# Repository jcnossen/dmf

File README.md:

# dmf
Prototype for electrowetting and digital microfluidics

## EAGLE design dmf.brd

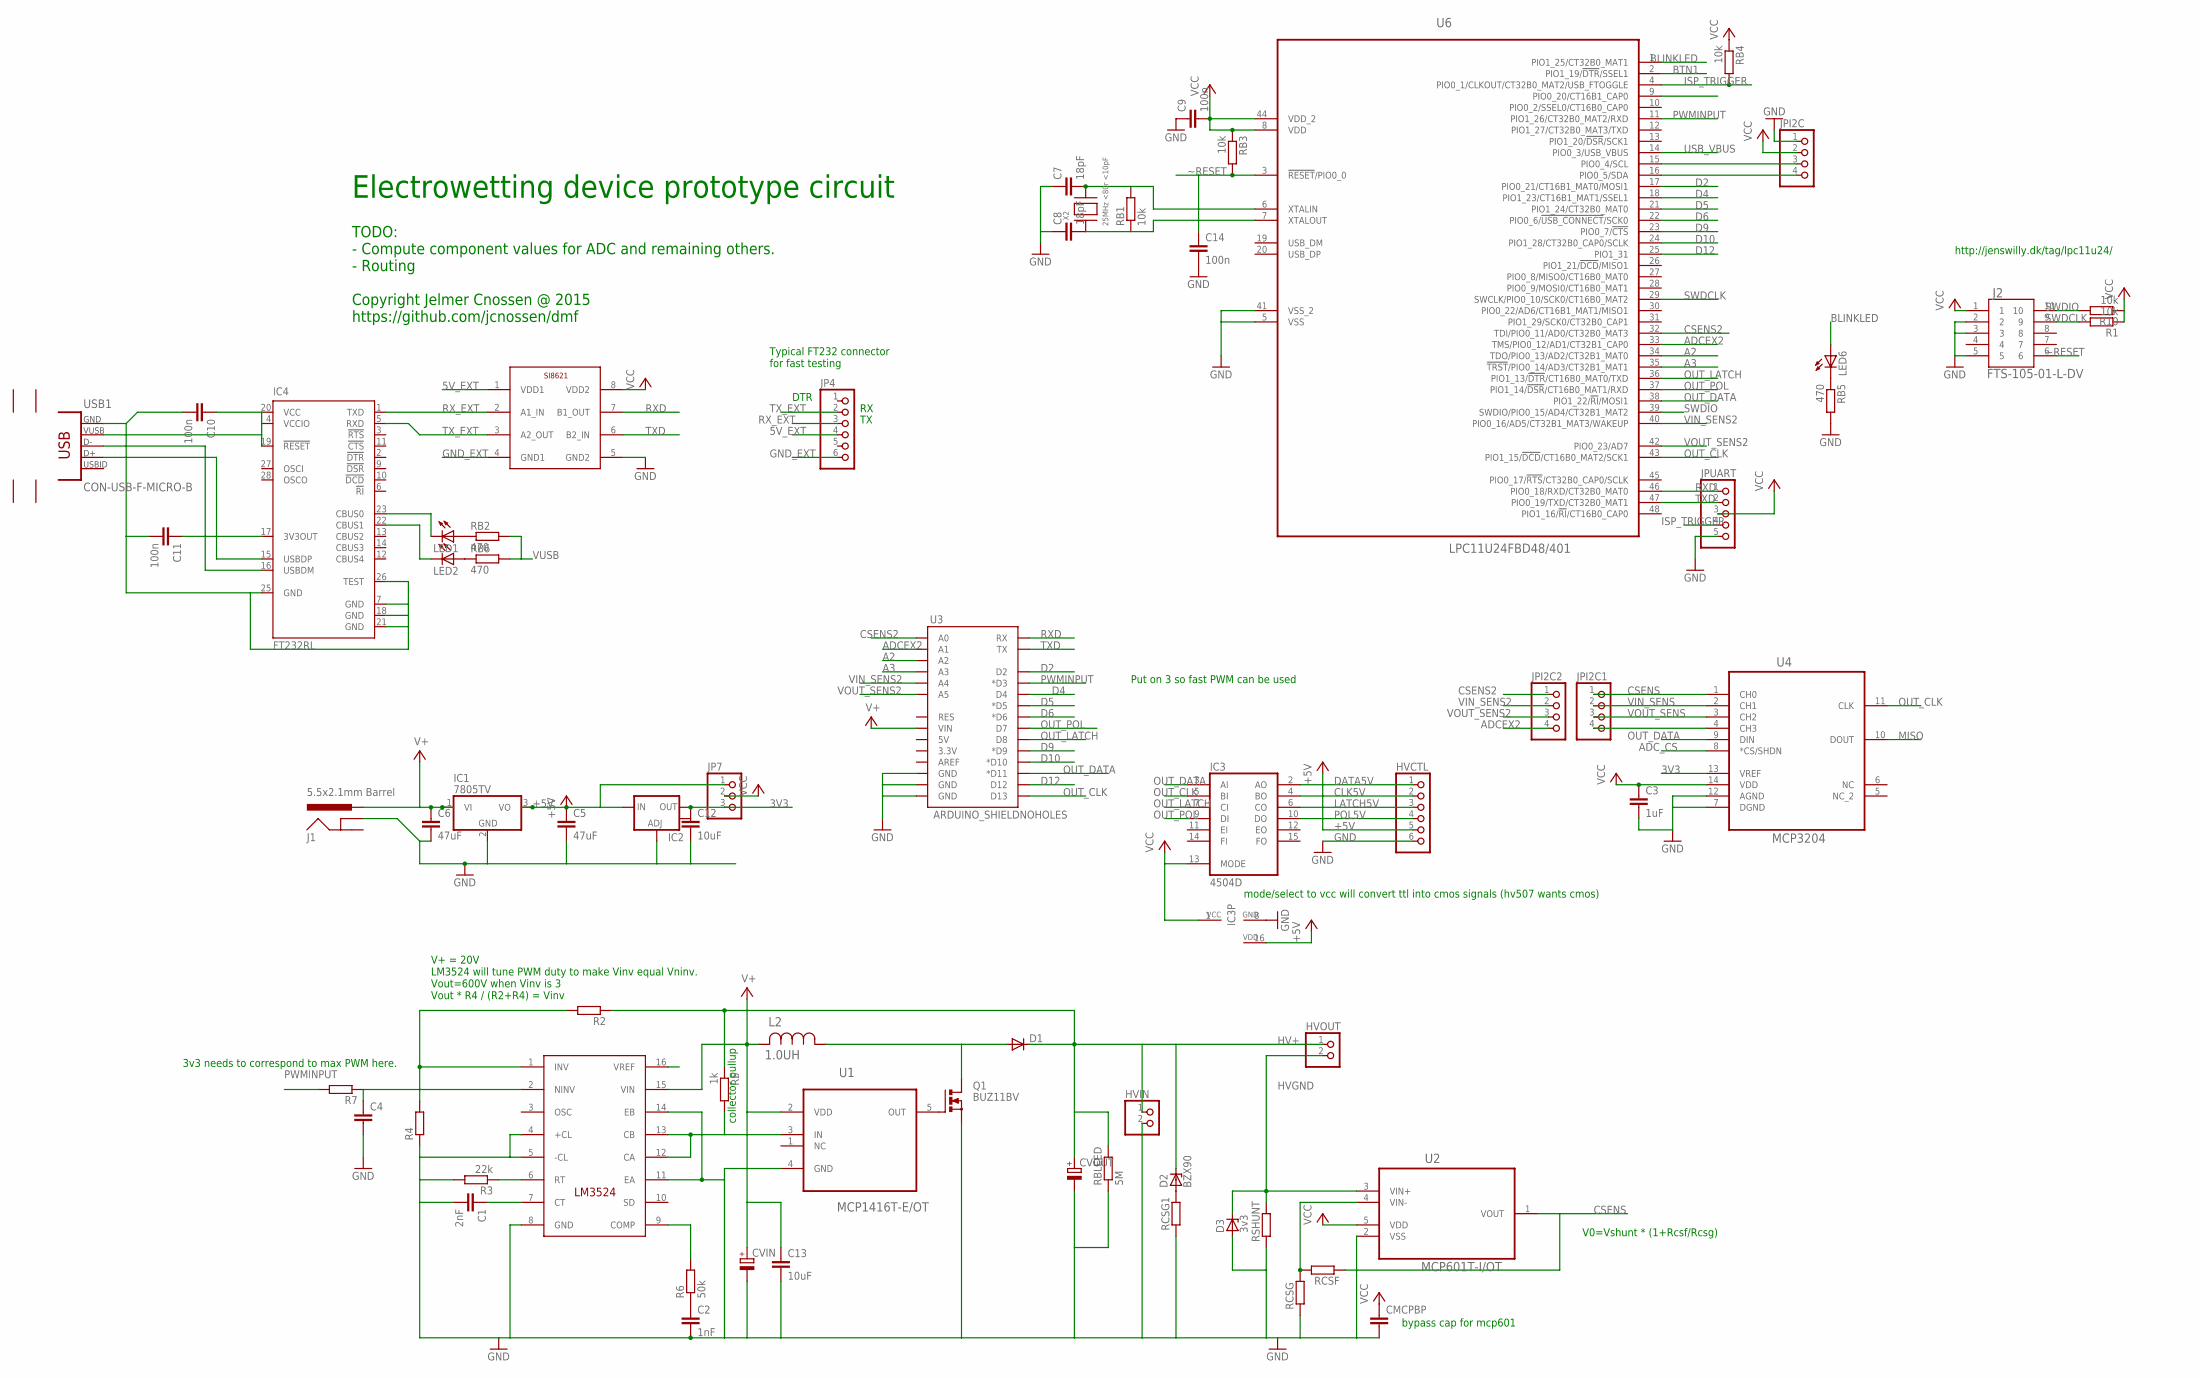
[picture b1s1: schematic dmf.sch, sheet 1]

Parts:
C1: 2nF; C0805
C2: 1nF; C0805
C3: 1uF; C0805
C4: C-EUC0805; C0805
C5, C6: 47uF; C1206
C7, C8: 18pF; C0805
C9, C10, C11, C14: 100n; C0805
C12: 10uF; C1206
C13: 10uF; C0805
CMCPBP: C-EUC0805; C0805
CVIN: CPOL-EUE7.5-18; E7,5-18
CVOUT: CPOL-EUE7.5-18; E7,5-18
D1: DIODE-SMB; SMB
D2: BZX90; DO34Z7
D3: 3v3; SMB
HVCTL: PINHD-1X06_2.54-S; 1X06-S
HVIN: PINHD-1X02_2.54; 1X02
HVOUT: PINHD-1X02_2.54; 1X02
IC1: 7805TV; TO220V
IC2: V_REG_LM1117SOT223; SOT223
IC3: 4504D; SO16
IC4: FT232RL; SSOP28
J1: 5.5x2.1mm Barrel; POWER_JACK_SMD
J2: FTS-105-01-L-DV; SAMTEC_FTS-105-01-L-DV
JP4: PINHD-1X06_2.54-S; 1X06-S
JP7: PINHD-1X03_2.54-S; 1X03-S
JPI2C, JPI2C1, JPI2C2: PINHD-1X04_2.54-S; 1X04-S
JPUART: PINHD-1X05_2.54-S; 1X05-S
L2: 1.0UH; IND_ELL6XH
LED1, LED2, LED6: LEDCHIP-LED0805; CHIP-LED0805
Q1: BUZ11BV; TO220BV
R1, R10: 10k; R0603
R2, R4, R7: R-EU_R0603; R0603
R3: 22k; R0603
R5: 1k; R0603
R6: 50k; R0603
RB1, RB3, RB4: 10k; R0603
RB2, RB6: 470; R0603
RB5: 470; R0402
RBLEED: 5M; R1206
RCSF: R-EU_R0603; R0603
RCSG: R-EU_R0603; R0603
RCSG1: R-EU_R1206; R1206
RSHUNT: R-EU_R1206; R1206
U1: MCP1416T-E/OT; SOT95P270X145-5N
U2: MCP601T-I/OT; SOT95P320X145-5N
U3: ARDUINO_SHIELDNOHOLES; DUEMILANOVE_SHIELD_NOHOLES
U4: MCP3204; SOIC127P600X175-14N
U6: LPC11U24FBD48/401; QFP50P900X900X160-48N
U$1: LM3524; SO16
U$2: SI8621AB; SO8
USB1: CON-USB-F-MICRO-B; CONN_USB_MICRO-B
X2: 25MHz <80r <10pF; NX5032

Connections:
3V3: C12.1, IC2.2 (OUT), JP7.3, U4.13 (VREF)
5V_EXT: JP4.4, U$2.1 (VDD1)
+5V: C5.1, HVCTL.5, IC1.3 (VO), IC2.3 (IN), IC3.16 (VDD), JP7.1
A2: U3.A2, U6.34 (TDO/PIO0_13/AD2/CT32B1_MAT0)
A3: U3.A3, U6.35 (!TRST!/PIO0_14/AD3/CT32B1_MAT1)
ADCEX: JPI2C1.4, U4.4 (CH3)
ADCEX2: JPI2C2.4, U3.A1, U6.33 (TMS/PIO0_12/AD1/CT32B1_CAP0)
ADC_CS: U4.8 (*CS/SHDN)
BLINKLED: LED6.A, U6.1 (PIO1_25/CT32B0_MAT1)
BTN1: U6.2 (PIO1_19/!DTR!/SSEL1)
CLK5V: HVCTL.2, IC3.4 (BO)
COLLECTOR: R5.2, U1.3 (IN), U$1.12 (CA), U$1.13 (CB)
CSENS: JPI2C1.1, RCSF.1, U2.1 (VOUT), U4.1 (CH0)
CSENS2: JPI2C2.1, U3.A0, U6.32 (TDI/PIO0_11/AD0/CT32B0_MAT3)
D2: U3.D2, U6.17 (PIO0_21/CT16B1_MAT0/MOSI1)
D4: U3.D4, U6.18 (PIO1_23/CT16B1_MAT1/SSEL1)
D5: U3.D5 (*D5), U6.21 (PIO1_24/CT32B0_MAT0)
D6: U3.D6 (*D6), U6.22 (PIO0_6/!USB_CONNECT!/SCK0)
D9: U3.D9 (*D9), U6.23 (PIO0_7/!CTS)
D10: U3.D10 (*D10), U6.24 (PIO1_28/CT32B0_CAP0/SCLK)
D12: U3.D12, U6.25 (PIO1_31)
DATA5V: HVCTL.1, IC3.2 (AO)
GND: C1.2, C2.2, C3.2, C4.2, C5.2, C6.2, C7.1, C8.1, C9.1, C12.2, C13.2, C14.2, CMCPBP.2, CVIN.-, CVOUT.-, D3.A, HVCTL.6, HVIN.2, IC1.2 (GND), IC2.1 (ADJ), IC3.8 (GND), J1.GND (GNDBREAK), J2.2, J2.3, J2.5, JPI2C.1, JPUART.5, Q1.S, R3.2, R4.1, RB5.2, RBLEED.1, RCSG.1, RCSG1.1, RSHUNT.1, U1.4 (GND), U2.2 (VSS), U3.GND@0 (GND), U3.GND@1 (GND), U3.GND@2 (GND), U4.7 (DGND), U4.12 (AGND), U6.5 (VSS), U6.41 (VSS_2), U$1.4 (+CL), U$1.5 (-CL), U$1.8 (GND), U$1.11 (EA), U$1.14 (EB), U$2.5 (GND2)
GND_EXT: C10.2, C11.2, IC4.7 (GND), IC4.18 (GND), IC4.21 (GND), IC4.25 (GND), IC4.26 (TEST), JP4.6, U$2.4 (GND1), USB1.P5 (GND)
HV+: CVOUT.+, D1.C, D2.C, HVIN.1, HVOUT.1, R2.1, R5.1, RBLEED.2
HVGND: D3.C, HVOUT.2, RSHUNT.2, U2.3 (VIN+)
ISP_TRIGGER: JPUART.4, RB4.2, U6.4 (PIO0_1/CLKOUT/CT32B0_MAT2/USB_FTOGGLE)
LATCH5V: HVCTL.3, IC3.6 (CO)
MISO: U4.10 (DOUT)
unnamed: C2.1, R6.1
unnamed: C1.1, U$1.7 (CT)
unnamed: R2.2, R4.2, U$1.1 (INV)
unnamed: R3.1, U$1.6 (RT)
unnamed: R6.2, U$1.9 (COMP)
unnamed: D1.A, L2.1, Q1.D
unnamed: Q1.G, U1.5 (OUT)
unnamed: RCSF.2, RCSG.2, U2.4 (VIN-)
unnamed: D2.A, RCSG1.2
unnamed: C4.1, R7.1, U$1.2 (NINV)
unnamed: IC4.16 (USBDM), USB1.P2 (D-)
unnamed: IC4.15 (USBDP), USB1.P3 (D+)
unnamed: C11.1, IC4.17 (3V3OUT)
unnamed: IC4.23 (CBUS0), LED1.C
unnamed: IC4.22 (CBUS1), LED2.C
unnamed: LED1.A, RB2.1
unnamed: LED2.A, RB6.1
unnamed: C8.2, RB1.1, U6.7 (XTALOUT), X2.P$1
unnamed: LED6.C, RB5.1
unnamed: C7.2, RB1.2, U6.6 (XTALIN), X2.P$2
OUT_CLK: IC3.5 (BI), U3.D13, U4.11 (CLK), U6.43 (PIO1_15/!DCD!/CT16B0_MAT2/SCK1)
OUT_DATA: IC3.3 (AI), U3.D11 (*D11), U4.9 (DIN), U6.38 (PIO1_22/!RI!/MOSI1)
OUT_LATCH: IC3.7 (CI), U3.D8, U6.36 (PIO1_13/!DTR!/CT16B0_MAT0/TXD)
OUT_POL: IC3.9 (DI), U3.D7, U6.37 (PIO1_14/!DSR!/CT16B0_MAT1/RXD)
POL5V: HVCTL.4, IC3.10 (DO)
PWMINPUT: R7.2, U3.D3 (*D3), U6.11 (PIO1_26/CT32B0_MAT2/RXD)
RXD: JPUART.1, U3.RX, U6.46 (PIO0_18/RXD/CT32B0_MAT0), U$2.7 (B1_OUT)
RX_EXT: IC4.1 (TXD), JP4.3, U$2.2 (A1_IN)
SCL: JPI2C.3, U6.15 (PIO0_4/SCL)
SDA: JPI2C.4, U6.16 (PIO0_5/SDA)
SWDCLK: J2.9, R1.2, U6.29 (SWCLK/PIO0_10/SCK0/CT16B0_MAT2)
SWDIO: J2.10, R10.2, U6.39 (SWDIO/PIO0_15/AD4/CT32B1_MAT2)
TXD: JPUART.2, U3.TX, U6.47 (PIO0_19/TXD/CT32B0_MAT1), U$2.6 (B2_IN)
TX_EXT: IC4.5 (RXD), JP4.2, U$2.3 (A2_OUT)
USB_VBUS: U6.14 (PIO0_3/USB_VBUS)
V+: C6.1, C13.1, CVIN.+, IC1.1 (VI), J1.VIN0 (PWR), L2.2, U1.2 (VDD), U3.VIN, U$1.15 (VIN)
VCC: C3.1, C9.2, CMCPBP.1, IC3.1 (VCC), IC3.13 (MODE), J2.1, JP7.2, JPI2C.2, JPUART.3, R1.1, R10.1, RB3.1, RB4.1, U2.5 (VDD), U4.14 (VDD), U6.8 (VDD), U6.44 (VDD_2), U$2.8 (VDD2)
VIN_SENS: JPI2C1.2, U4.2 (CH1)
VIN_SENS2: JPI2C2.2, U3.A4, U6.40 (PIO0_16/AD5/CT32B1_MAT3/WAKEUP)
VOUT_SENS: JPI2C1.3, U4.3 (CH2)
VOUT_SENS2: JPI2C2.3, U3.A5, U6.42 (PIO0_23/AD7)
VUSB: C10.1, IC4.4 (VCCIO), IC4.19 (!RESET), IC4.20 (VCC), RB2.2, RB6.2, USB1.P1 (VUSB)
~RESET: C14.1, J2.6, RB3.2, U6.3 (!RESET!/PIO0_0)

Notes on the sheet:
V0=Vshunt * (1+Rcsf/Rcsg)
bypass cap for mcp601
V+ = 20V LM3524 will tune PWM duty to make Vinv equal Vninv. Vout=600V when Vinv is 3 Vout * R4 / (R2+R4) = Vinv
3v3 needs to correspond to max PWM here.
Put on 3 so fast PWM can be used
mode/select to vcc will convert ttl into cmos signals (hv507 wants cmos)
DTR
Typical FT232 connector for fast testing
http://jenswilly.dk/tag/lpc11u24/
collector pullup
TODO: - Compute component values for ADC and remaining others. - Routing Copyright Jelmer Cnossen @ 2015 https://github.com/jcnossen/dmf
Electrowetting device prototype circuit

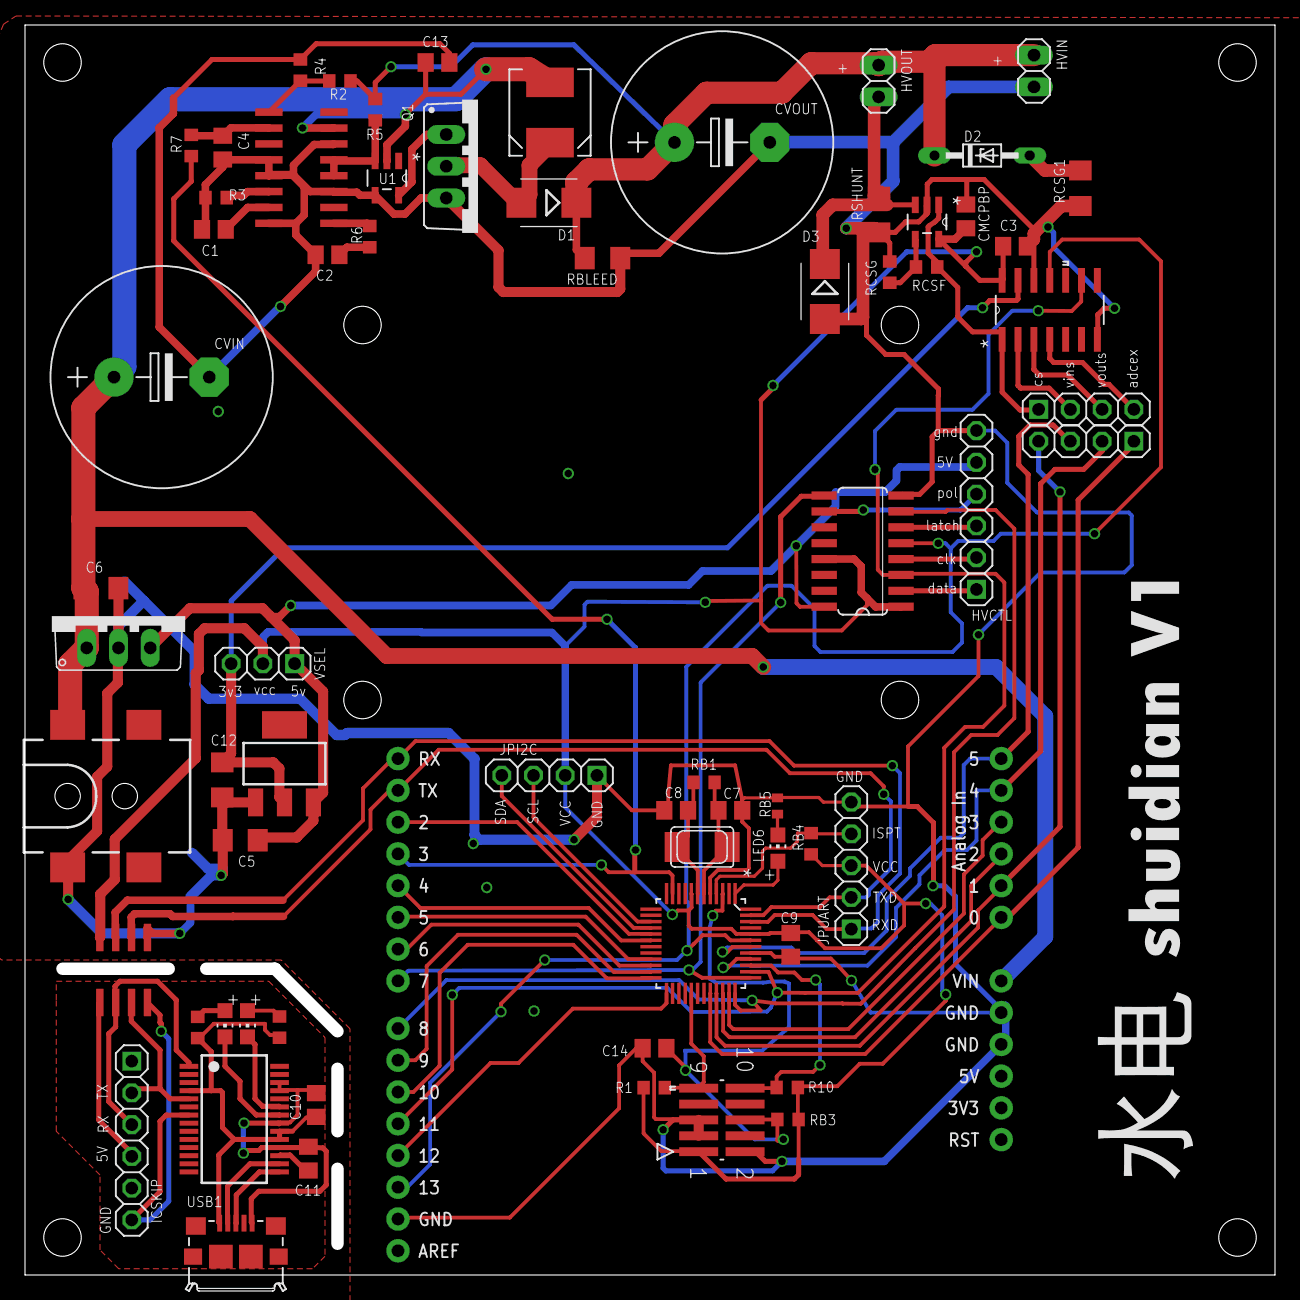
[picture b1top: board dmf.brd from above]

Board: 2 copper layers, 100.0 x 100.0 mm, 68 parts (0 on the bottom side), 68 nets.

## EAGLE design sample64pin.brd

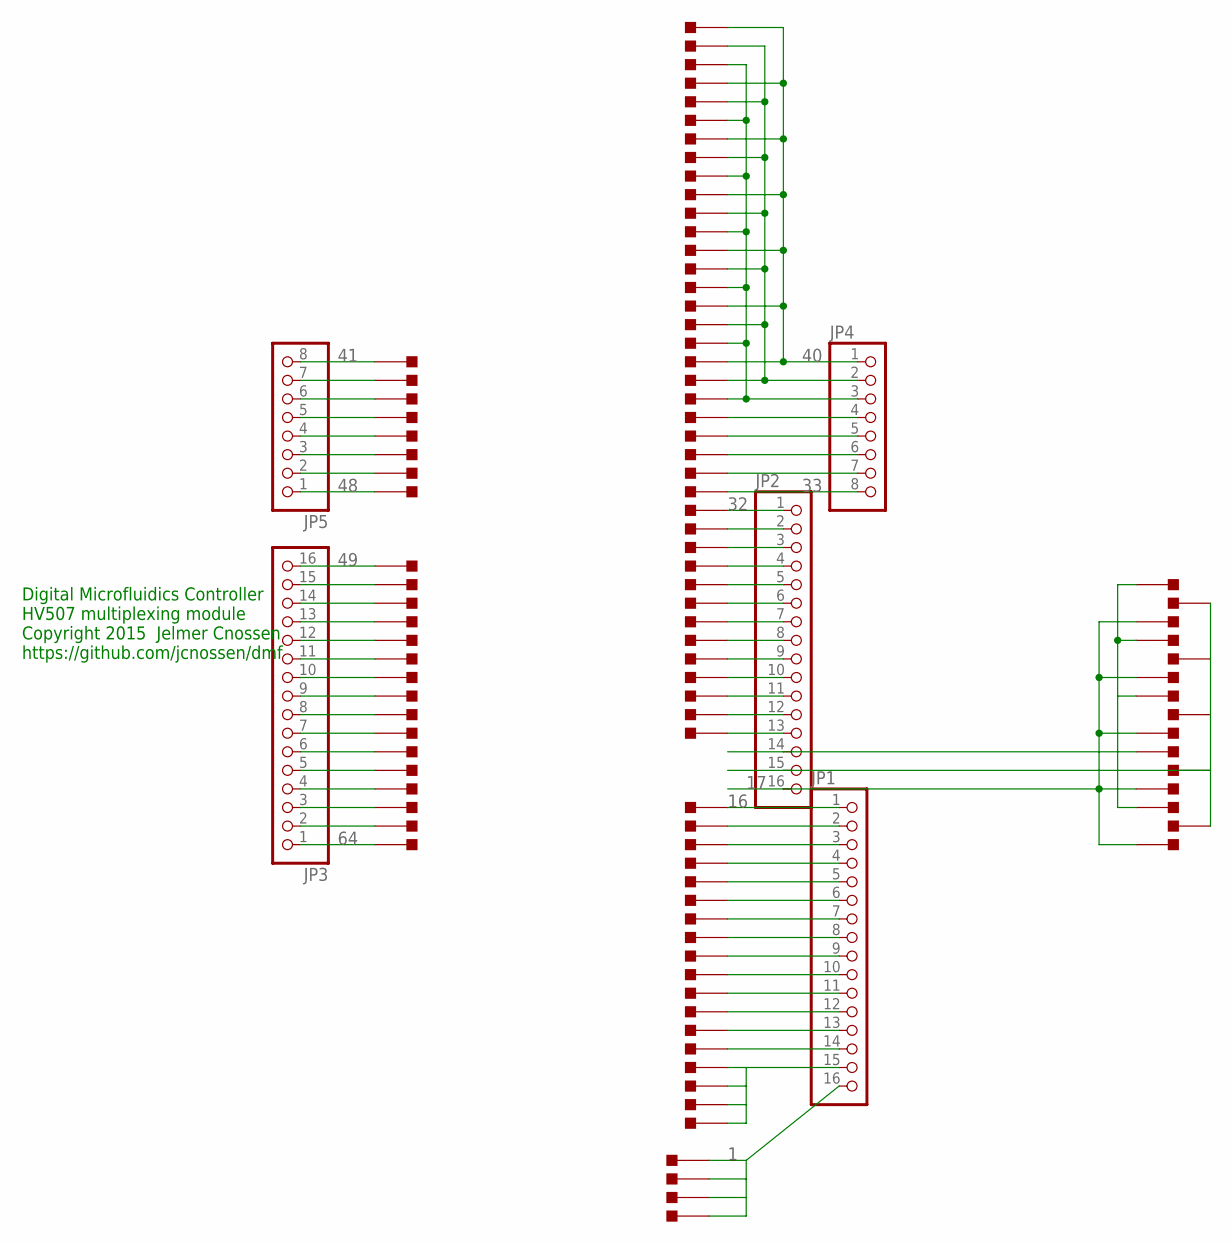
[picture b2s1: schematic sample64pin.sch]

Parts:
JP1, JP2, JP3: PINHD-1X16_2.54-S; 1X16-S
JP4, JP5: PINHD-1X08_2.54-S; 1X08-S
U$1, U$2, U$3, U$4, U$5, U$6, U$7, U$8, U$9, U$10, U$11, U$12, U$13, U$14, U$15, U$16, U$17, U$18, U$19, U$20, U$21, U$22, U$23, U$24, U$25, U$26, U$27, U$28, U$29, U$30, U$31, U$32, U$33, U$34, U$35, U$36, U$37, U$38, U$39, U$40, U$41, U$42, U$43, U$44, U$45, U$46, U$47, U$48, U$49, U$50, U$51, U$52, U$53, U$54, U$55, U$56, U$57, U$58, U$59, U$60, U$61, U$62, U$63, U$64, U$65, U$66, U$67, U$68, U$69, U$70, U$71, U$72, U$73, U$74, U$75, U$76, U$77, U$78, U$79, U$80, U$81, U$82, U$83, U$84, U$85, U$86, U$87, U$88, U$89, U$90, U$91, U$92, U$93, U$94, U$95, U$96, U$97, U$98, U$99, U$100: ELECTRODE

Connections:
1: JP1.16, U$46.P$2, U$47.P$2, U$48.P$2, U$64.P$2
16: JP1.1, U$49.P$2
17: JP2.16, U$67.P$2, U$70.P$2, U$73.P$2, U$76.P$2, U$79.P$2
32: JP2.1, U$33.P$2
33: JP4.8, U$32.P$2
40: JP4.1, U$1.P$2, U$80.P$2, U$83.P$2, U$86.P$2, U$89.P$2, U$92.P$2, U$95.P$2
41: JP5.8, U$4.P$2
48: JP5.1, U$11.P$2
49: JP3.16, U$12.P$2
64: JP3.1, U$27.P$2
unnamed: JP2.14, U$65.P$2, U$68.P$2, U$71.P$2, U$74.P$2, U$77.P$2
unnamed: JP1.2, U$50.P$2
unnamed: JP1.3, U$51.P$2
unnamed: JP1.4, U$52.P$2
unnamed: JP1.5, U$53.P$2
unnamed: JP1.6, U$54.P$2
unnamed: JP1.7, U$55.P$2
unnamed: JP1.8, U$56.P$2
unnamed: JP1.9, U$57.P$2
unnamed: JP1.10, U$58.P$2
unnamed: JP1.11, U$59.P$2
unnamed: JP1.12, U$60.P$2
unnamed: JP1.13, U$61.P$2
unnamed: JP1.14, U$62.P$2
unnamed: JP1.15, U$63.P$2, U$98.P$2, U$99.P$2, U$100.P$2
unnamed: JP2.15, U$66.P$2, U$69.P$2, U$72.P$2, U$75.P$2, U$78.P$2
unnamed: JP2.2, U$34.P$2
unnamed: JP2.3, U$35.P$2
unnamed: JP2.4, U$36.P$2
unnamed: JP2.5, U$37.P$2
unnamed: JP2.6, U$38.P$2
unnamed: JP2.7, U$39.P$2
unnamed: JP2.8, U$40.P$2
unnamed: JP2.9, U$41.P$2
unnamed: JP2.10, U$42.P$2
unnamed: JP2.11, U$43.P$2
unnamed: JP2.12, U$44.P$2
unnamed: JP2.13, U$45.P$2
unnamed: JP3.2, U$26.P$2
unnamed: JP3.3, U$25.P$2
unnamed: JP3.4, U$24.P$2
unnamed: JP3.5, U$23.P$2
unnamed: JP3.6, U$22.P$2
unnamed: JP3.7, U$21.P$2
unnamed: JP3.8, U$20.P$2
unnamed: JP3.9, U$19.P$2
unnamed: JP3.10, U$18.P$2
unnamed: JP3.11, U$17.P$2
unnamed: JP3.12, U$16.P$2
unnamed: JP3.13, U$15.P$2
unnamed: JP3.14, U$14.P$2
unnamed: JP3.15, U$13.P$2
unnamed: JP4.2, U$2.P$2, U$81.P$2, U$84.P$2, U$87.P$2, U$90.P$2, U$93.P$2, U$96.P$2
unnamed: JP4.3, U$3.P$2, U$82.P$2, U$85.P$2, U$88.P$2, U$91.P$2, U$94.P$2, U$97.P$2
unnamed: JP4.4, U$28.P$2
unnamed: JP4.5, U$29.P$2
unnamed: JP4.6, U$30.P$2
unnamed: JP4.7, U$31.P$2
unnamed: JP5.2, U$10.P$2
unnamed: JP5.3, U$9.P$2
unnamed: JP5.4, U$8.P$2
unnamed: JP5.5, U$7.P$2
unnamed: JP5.6, U$6.P$2
unnamed: JP5.7, U$5.P$2

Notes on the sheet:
Digital Microfluidics Controller HV507 multiplexing module Copyright 2015 Jelmer Cnossen https://github.com/jcnossen/dmf

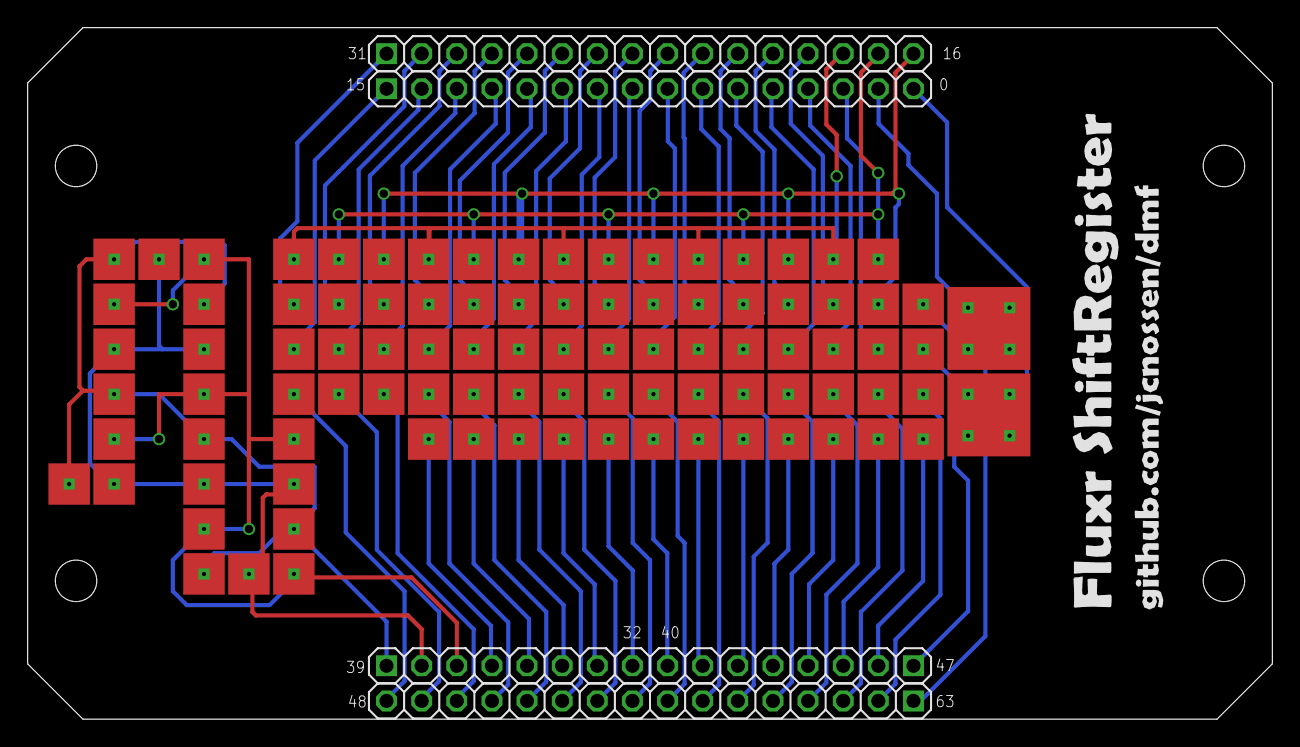
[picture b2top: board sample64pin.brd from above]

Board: 2 copper layers, 90.0 x 50.0 mm, 105 parts (0 on the bottom side), 64 nets.

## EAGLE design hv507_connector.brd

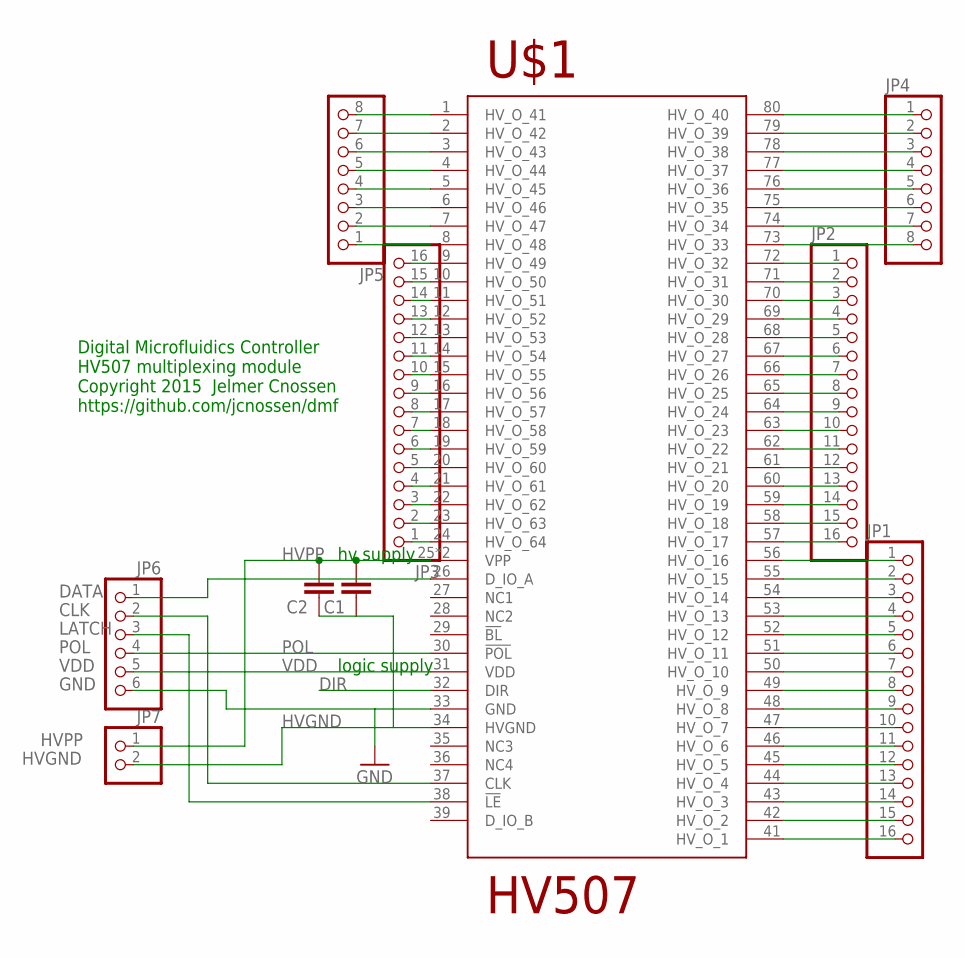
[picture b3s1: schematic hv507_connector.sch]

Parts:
C1: C-EUC1812; C1812
C2: C-EUC1206; C1206
JP1, JP2, JP3: PINHD-1X16_2.54-S; 1X16-S
JP4, JP5: PINHD-1X08_2.54-S; 1X08-S
JP6: PINHD-1X06_2.54-S; 1X06-S
JP7: PINHD-1X02_2.54-S; 1X02-S
U$1: HV507; HV507PG-G

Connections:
1: JP1.16, U$1.41 (HV_O_1)
16: JP1.1, U$1.56 (HV_O_16)
17: JP2.16, U$1.57 (HV_O_17)
32: JP2.1, U$1.72 (HV_O_32)
33: JP4.8, U$1.73 (HV_O_33)
40: JP4.1, U$1.80 (HV_O_40)
41: JP5.8, U$1.1 (HV_O_41)
48: JP5.1, U$1.8 (HV_O_48)
49: JP3.16, U$1.9 (HV_O_49)
64: JP3.1, U$1.24 (HV_O_64)
CLK: JP6.2, U$1.37 (CLK)
DATA: JP6.1, U$1.26 (D_IO_A)
DIR: U$1.32 (DIR)
GND: JP6.6, U$1.33 (GND)
HVGND: C1.1, C2.1, JP7.2, U$1.34 (HVGND)
HVPP: C1.2, C2.2, JP7.1, U$1.25 (VPP), U$1.40 (VPP)
LATCH: JP6.3, U$1.38 (!LE)
unnamed: JP1.2, U$1.55 (HV_O_15)
unnamed: JP1.3, U$1.54 (HV_O_14)
unnamed: JP1.4, U$1.53 (HV_O_13)
unnamed: JP1.5, U$1.52 (HV_O_12)
unnamed: JP1.6, U$1.51 (HV_O_11)
unnamed: JP1.7, U$1.50 (HV_O_10)
unnamed: JP1.8, U$1.49 (HV_O_9)
unnamed: JP1.9, U$1.48 (HV_O_8)
unnamed: JP1.10, U$1.47 (HV_O_7)
unnamed: JP1.11, U$1.46 (HV_O_6)
unnamed: JP1.12, U$1.45 (HV_O_5)
unnamed: JP1.13, U$1.44 (HV_O_4)
unnamed: JP1.14, U$1.43 (HV_O_3)
unnamed: JP1.15, U$1.42 (HV_O_2)
unnamed: JP2.2, U$1.71 (HV_O_31)
unnamed: JP2.3, U$1.70 (HV_O_30)
unnamed: JP2.4, U$1.69 (HV_O_29)
unnamed: JP2.5, U$1.68 (HV_O_28)
unnamed: JP2.6, U$1.67 (HV_O_27)
unnamed: JP2.7, U$1.66 (HV_O_26)
unnamed: JP2.8, U$1.65 (HV_O_25)
unnamed: JP2.9, U$1.64 (HV_O_24)
unnamed: JP2.10, U$1.63 (HV_O_23)
unnamed: JP2.11, U$1.62 (HV_O_22)
unnamed: JP2.12, U$1.61 (HV_O_21)
unnamed: JP2.13, U$1.60 (HV_O_20)
unnamed: JP2.14, U$1.59 (HV_O_19)
unnamed: JP2.15, U$1.58 (HV_O_18)
unnamed: JP3.2, U$1.23 (HV_O_63)
unnamed: JP3.3, U$1.22 (HV_O_62)
unnamed: JP3.4, U$1.21 (HV_O_61)
unnamed: JP3.5, U$1.20 (HV_O_60)
unnamed: JP3.6, U$1.19 (HV_O_59)
unnamed: JP3.7, U$1.18 (HV_O_58)
unnamed: JP3.8, U$1.17 (HV_O_57)
unnamed: JP3.9, U$1.16 (HV_O_56)
unnamed: JP3.10, U$1.15 (HV_O_55)
unnamed: JP3.11, U$1.14 (HV_O_54)
unnamed: JP3.12, U$1.13 (HV_O_53)
unnamed: JP3.13, U$1.12 (HV_O_52)
unnamed: JP3.14, U$1.11 (HV_O_51)
unnamed: JP3.15, U$1.10 (HV_O_50)
unnamed: JP4.2, U$1.79 (HV_O_39)
unnamed: JP4.3, U$1.78 (HV_O_38)
unnamed: JP4.4, U$1.77 (HV_O_37)
unnamed: JP4.5, U$1.76 (HV_O_36)
unnamed: JP4.6, U$1.75 (HV_O_35)
unnamed: JP4.7, U$1.74 (HV_O_34)
unnamed: JP5.2, U$1.7 (HV_O_47)
unnamed: JP5.3, U$1.6 (HV_O_46)
unnamed: JP5.4, U$1.5 (HV_O_45)
unnamed: JP5.5, U$1.4 (HV_O_44)
unnamed: JP5.6, U$1.3 (HV_O_43)
unnamed: JP5.7, U$1.2 (HV_O_42)
POL: JP6.4, U$1.30 (!POL)
VDD: JP6.5, U$1.31 (VDD)

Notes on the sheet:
logic supply
hv supply
Digital Microfluidics Controller HV507 multiplexing module Copyright 2015 Jelmer Cnossen https://github.com/jcnossen/dmf

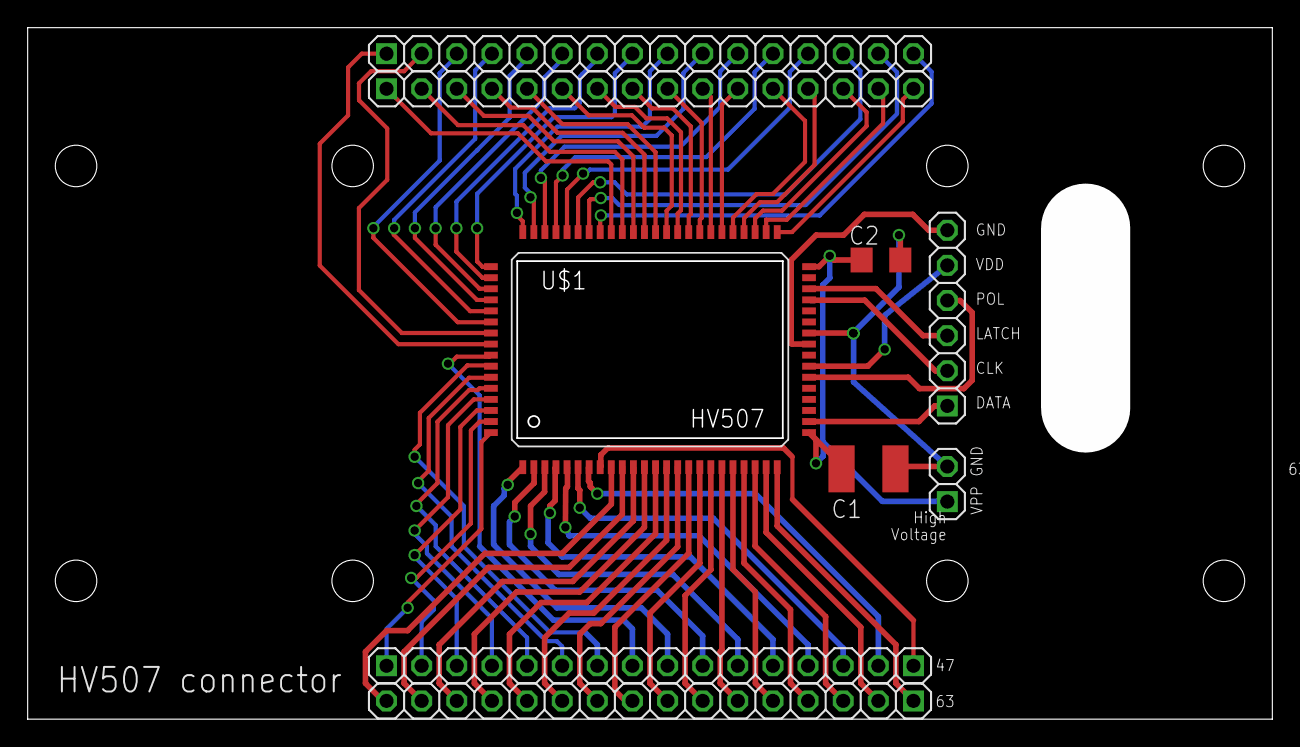
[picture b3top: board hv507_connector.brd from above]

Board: 2 copper layers, 90.0 x 50.0 mm, 10 parts (0 on the bottom side), 72 nets.

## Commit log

2015-09-22 * Eagle schematics upload
2015-09-27 overview
2015-09-27 dmf.brd routing
2015-09-29 ESP part library (from https://github.com/wvanvlaenderen/ESP8266-Eagle_Library)
2015-10-06 * DMF board first iteration
2015-10-09 * sample64pin

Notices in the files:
parts and their libraries:
SparkFun-PowerIC: Licensing: CC v3.0 Share-Alike You are welcome to use this library for commercial purposes.
